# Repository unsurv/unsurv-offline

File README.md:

# unsurv-offline

Currently available on [crowdsupply](https://www.crowdsupply.com/unsurv-technologies/unsurv-offline)

This project is part of the unsurv framework to fight privacy invasive technologies in the offline world. unsurv-offline logs your encounters with surveillance cameras and creates a daily report for you via NFC to review in the unsurv-companion Android app.

Demo: https://vimeo.com/497241039

This device can easily be adapted to different use cases via the Arduino IDE. Arduino library + board integration are planned.

List of features

- ESP32 D4
- ublox M8C GNSS receiver
- RF430CL330H NFC 
- BMA400 accelerometer
- SD card reader
- MCP73831 single cell LiPo charging
- CH340 USB to Serial

Software:
- [unsurv-offline](https://github.com/unsurv/unsurv-offline/tree/master/software/unsurv-offline)
- [other examples](https://github.com/unsurv/unsurv-offline/tree/master/software/examples) (tap to log location, location logging + step counting)

Hardware:
- [PCB design](https://github.com/unsurv/unsurv-offline/tree/master/unsurv_offline_pcb/main) (KiCad files)
- [case design](https://github.com/unsurv/unsurv-offline/tree/master/case) (FreeCAD + STL files)

Special thanks to:

- SparkFun for maintaining the [ublox library](https://github.com/sparkfun/SparkFun_Ublox_Arduino_Library)
- [awong1900](https://github.com/awong1900/RF430CL330H_Shield) for his work on the RF430
- [kriswiner](https://github.com/kriswiner/BMA400) for his BMA400 library

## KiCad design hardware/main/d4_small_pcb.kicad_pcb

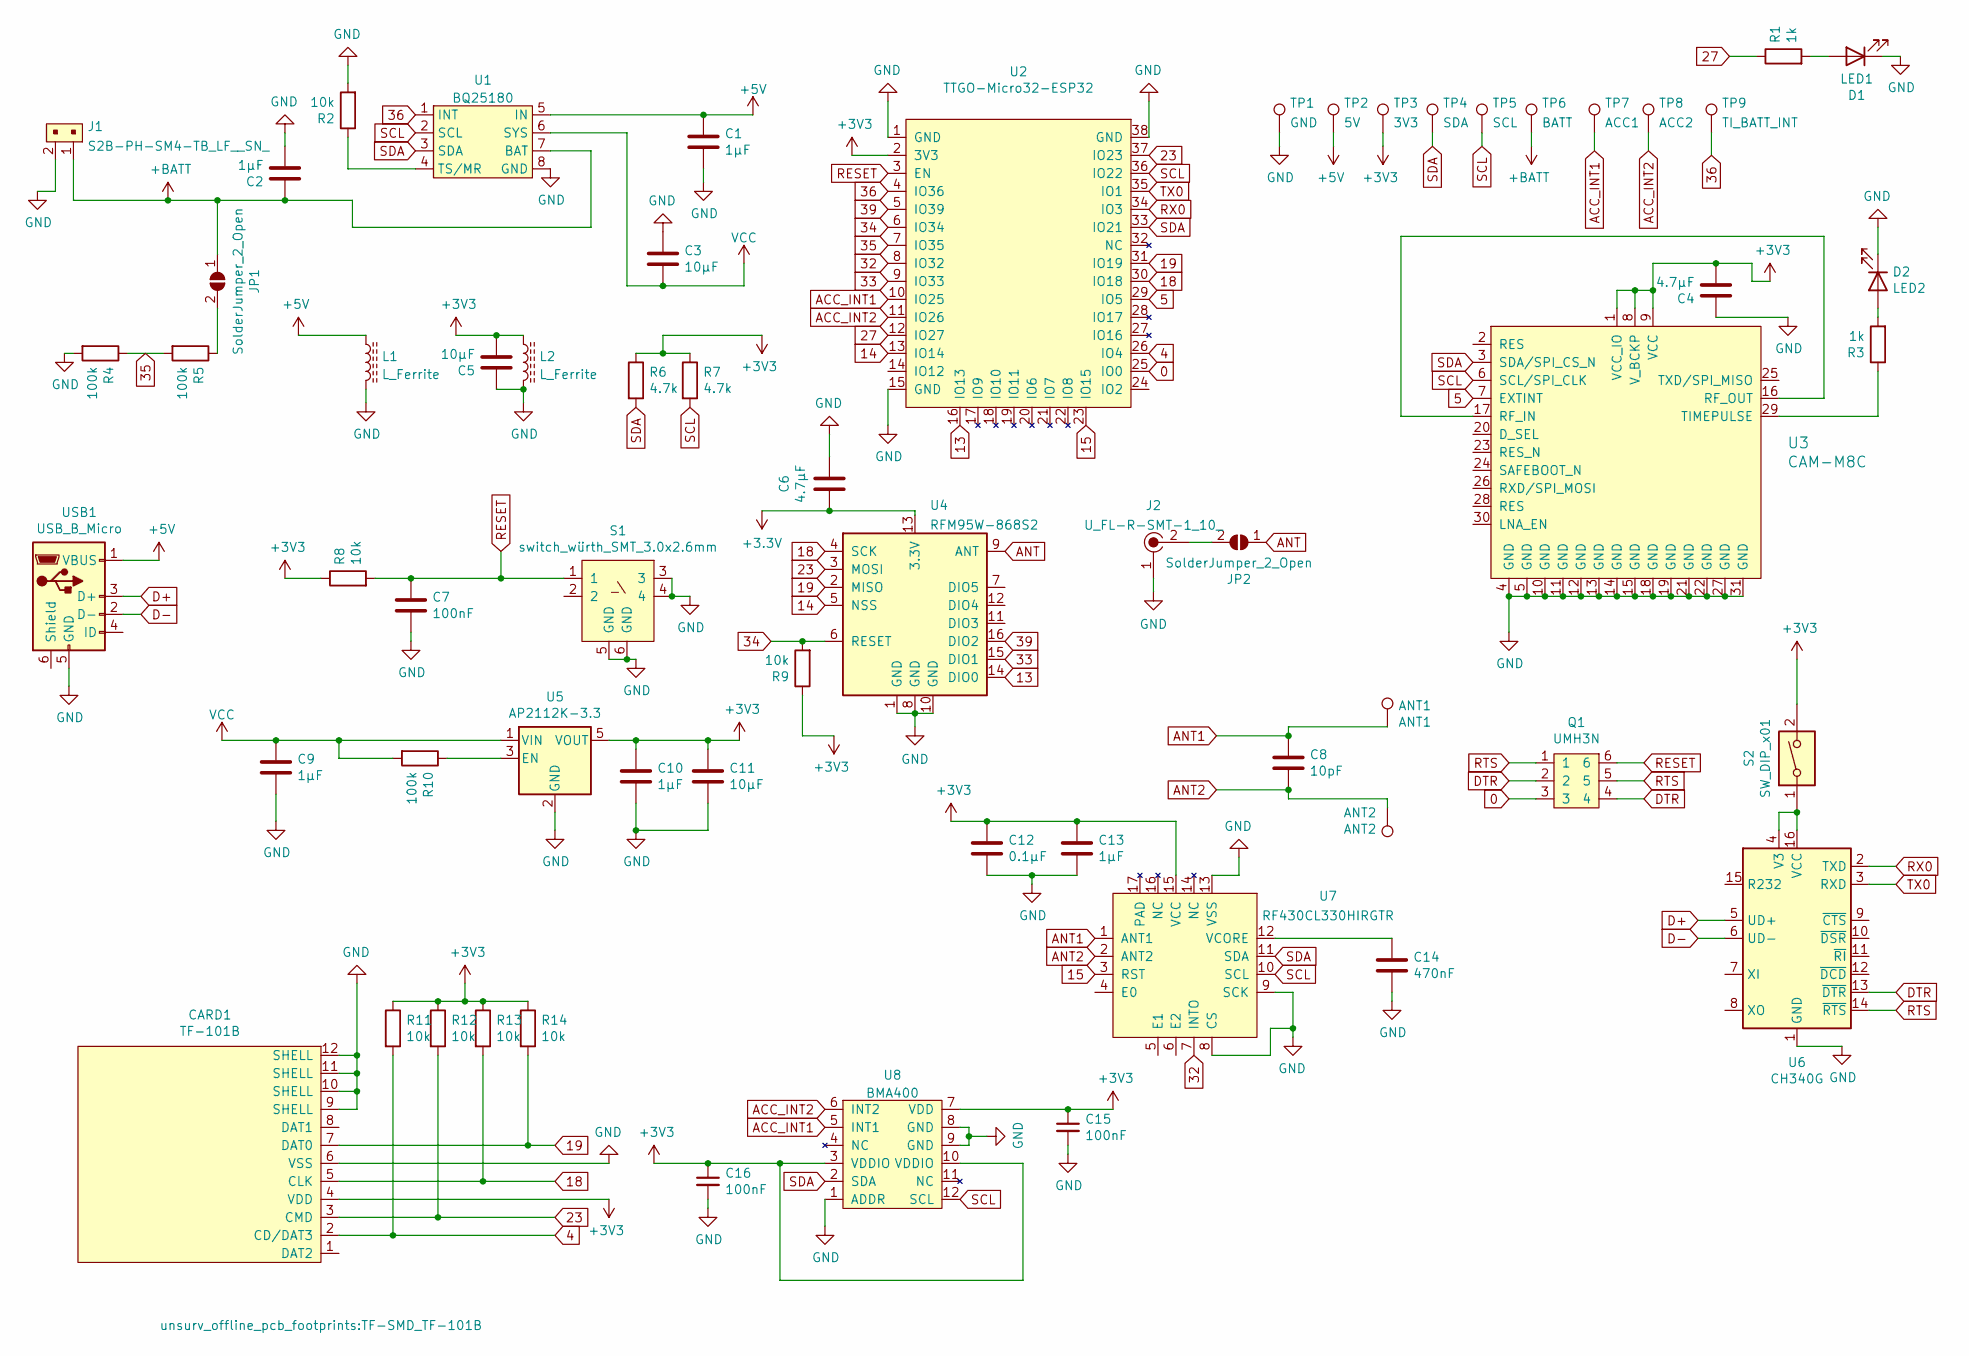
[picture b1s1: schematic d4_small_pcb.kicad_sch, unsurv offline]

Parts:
ANT1: ANT1; PogoPin_2_2mm_circular; MPN P70-1010045R
ANT2: ANT2; PogoPin_2_2mm_circular; MPN P70-1010045R
C1, C2, C9, C10, C13: 1µF; C_0603_1608Metric
C3, C5, C11: 10µF; C_0603_1608Metric
C4, C6: 4.7µF; C_0603_1608Metric
C7, C15, C16: 100nF; C_0603_1608Metric
C8: 10pF; C_0603_1608Metric
C12: 0.1µF; C_0603_1608Metric
C14: 470nF; C_0603_1608Metric
CARD1: TF-101B; TF-SMD_TF-101B; MPN TF-101B
D1: LED1; LED_0603
D2: LED2; LED_0603
J1: S2B-PH-SM4-TB_LF__SN_; PinHeader_2x1mm_P2mm_SMD_RA; MPN S2B-PH-SM4-TB(LF)(SN); Digi-Key_PN 455-1749-1-ND
J2: U_FL-R-SMT-1_10_; Coax_Conn_U.FL; MPN U.FL-R-SMT-1(10); Digi-Key_PN H11891CT-ND
JP1, JP2: SolderJumper_2_Open; SolderJumper-2_P1.3mm_Open_RoundedPad1.0x1.5mm
L1, L2: L_Ferrite; L_0603_1608Metric
Q1: UMH3N
R1, R3: 1k; R_0603_1608Metric
R2, R8, R9, R11, R12, R13, R14: 10k; R_0603_1608Metric
R4, R5, R10: 100k; R_0603_1608Metric
R6, R7: 4.7k; R_0603_1608Metric
S1: switch_würth_SMT_3.0x2.6mm; würth_SMT_3.0x2.6mm; MPN 435171014816
S2: SW_DIP_x01; CHS-01TA; MPN CHS-01TA
TP1: GND; TestPoint_Pad_D1.0mm
TP2: 5V; TestPoint_Pad_D1.0mm
TP3: 3V3; TestPoint_Pad_D1.0mm
TP4: SDA; TestPoint_Pad_D1.0mm
TP5: SCL; TestPoint_Pad_D1.0mm
TP6: BATT; TestPoint_Pad_D1.0mm
TP7: ACC1; TestPoint_Pad_D1.0mm
TP8: ACC2; TestPoint_Pad_D1.0mm
TP9: TI_BATT_INT; TestPoint_Pad_D1.0mm
U1: BQ25180; MPN BQ25180YBGR
U2: TTGO-Micro32-ESP32
U3: CAM-M8C; GPS_Module_CAM-M8C-0; MPN CAM-M8C-0-10; Digi-Key_PN 672-CAM-M8C-0-10CT-ND
U4: RFM95W-868S2; HOPERF_RFM9XW_SMD
U5: AP2112K-3.3; SOT-23-5
U6: CH340G; SOIC-16_3.9x9.9mm_P1.27mm
U7: RF430CL330HIRGTR‎; RF430_3x3mm_regular; MPN RF430CL330HIRGTR
U8: BMA400; BMA400_regular
USB1: USB_B_Micro; USB_Micro-B_Amphenol_10103594-0001LF_Horizontal; MPN 10103594-0001LF

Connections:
0: Q1.3, U2.25 (IO0)
4: CARD1.2 (CD/DAT3), R11.2, U2.26 (IO4)
5: U2.29 (IO5), U3.7 (EXTINT)
13: U2.16 (IO13), U4.14 (DIO0)
14: U2.13 (IO14), U4.5 (NSS)
15: U2.23 (IO15), U7.3 (RST)
18: CARD1.5 (CLK), R13.2, U2.30 (IO18), U4.4 (SCK)
19: CARD1.7 (DAT0), R14.2, U2.31 (IO19), U4.2 (MISO)
23: CARD1.3 (CMD), R12.2, U2.37 (IO23), U4.3 (MOSI)
27: R1.1, U2.12 (IO27)
32: U2.8 (IO32), U7.7 (INTO)
33: U2.9 (IO33), U4.15 (DIO1)
34: R9.2, U2.6 (IO34), U4.6 (RESET)
35: R4.1, R5.2, U2.7 (IO35)
36: TP9.1, U1.1 (INT), U2.4 (IO36)
39: U2.5 (IO39), U4.16 (DIO2)
+3.3V: C6.2, U4.13 (3.3V)
+3V3: C4.2, C5.1, C10.2, C11.2, C12.1, C13.1, C15.1, C16.1, CARD1.4 (VDD), L2.1, R6.1, R7.1, R8.1, R9.1, R11.1, R12.1, R13.1, R14.1, S2.2, TP3.1, U2.2 (3V3), U3.1 (VCC_IO), U3.8 (V_BCKP), U3.9 (VCC), U5.5 (VOUT), U7.15 (VCC), U8.3 (VDDIO), U8.7 (VDD), U8.10 (VDDIO)
+5V: C1.2, L1.1, TP2.1, U1.5 (IN), USB1.1 (VBUS)
+BATT: C2.2, J1.1, JP1.1 (A), TP6.1, U1.7 (BAT)
ACC_INT1: TP7.1, U2.10 (IO25), U8.5 (INT1)
ACC_INT2: TP8.1, U2.11 (IO26), U8.6 (INT2)
ANT: JP2.1 (A), U4.9 (ANT)
ANT1: ANT1.1, C8.1, U7.1 (ANT1)
ANT2: ANT2.1, C8.2, U7.2 (ANT2)
D+: U6.5 (UD+), USB1.3 (D+)
D-: U6.6 (UD-), USB1.2 (D-)
DTR: Q1.2, Q1.4, U6.13 (~DTR)
GND: C1.1, C2.1, C3.2, C4.1, C5.2, C6.1, C7.2, C9.1, C10.1, C11.1, C12.2, C13.2, C14.2, C15.2, C16.2, CARD1.6 (VSS), CARD1.9 (SHELL), CARD1.10 (SHELL), CARD1.11 (SHELL), CARD1.12 (SHELL), D1.1 (K), D2.1 (K), J1.2, J2.1, L1.2, L2.2, R2.2, R4.2, S1.3, S1.4, S1.5 (GND), S1.6 (GND), TP1.1, U1.8 (GND), U2.1 (GND), U2.15 (GND), U2.38 (GND), U3.4 (GND), U3.5 (GND), U3.10 (GND), U3.11 (GND), U3.12 (GND), U3.13 (GND), U3.14 (GND), U3.15 (GND), U3.18 (GND), U3.19 (GND), U3.21 (GND), U3.22 (GND), U3.27 (GND), U3.31 (GND), U4.1 (GND), U4.8 (GND), U4.10 (GND), U5.2 (GND), U6.1 (GND), U7.8 (CS), U7.9 (SCK), U7.13 (VSS), U8.1 (ADDR), U8.8 (GND), U8.9 (GND), USB1.5 (GND)
unnamed: D1.2 (A), R1.2
unnamed: D2.2 (A), R3.2
unnamed: JP1.2 (B), R5.1
unnamed: J2.2, JP2.2 (B)
unnamed: R2.1, U1.4 (TS/MR)
unnamed: U3.16 (RF_OUT), U3.17 (RF_IN)
unnamed: R3.1, U3.29 (TIMEPULSE)
unnamed: R10.1, U5.3 (EN)
unnamed: S2.1, U6.4 (V3), U6.16 (VCC)
unnamed: C14.1, U7.12 (VCORE)
RESET: C7.1, Q1.6, R8.2, S1.1, U2.3 (EN)
RTS: Q1.1, Q1.5, U6.14 (~RTS)
RX0: U2.34 (IO3), U6.2 (TXD)
SCL: R7.2, TP5.1, U1.2 (SCL), U2.36 (IO22), U3.6 (SCL/SPI_CLK), U7.10 (SCL), U8.12 (SCL)
SDA: R6.2, TP4.1, U1.3 (SDA), U2.33 (IO21), U3.3 (SDA/SPI_CS_N), U7.11 (SDA), U8.2 (SDA)
TX0: U2.35 (IO1), U6.3 (RXD)
VCC: C3.1, C9.2, R10.2, U1.6 (SYS), U5.1 (VIN)

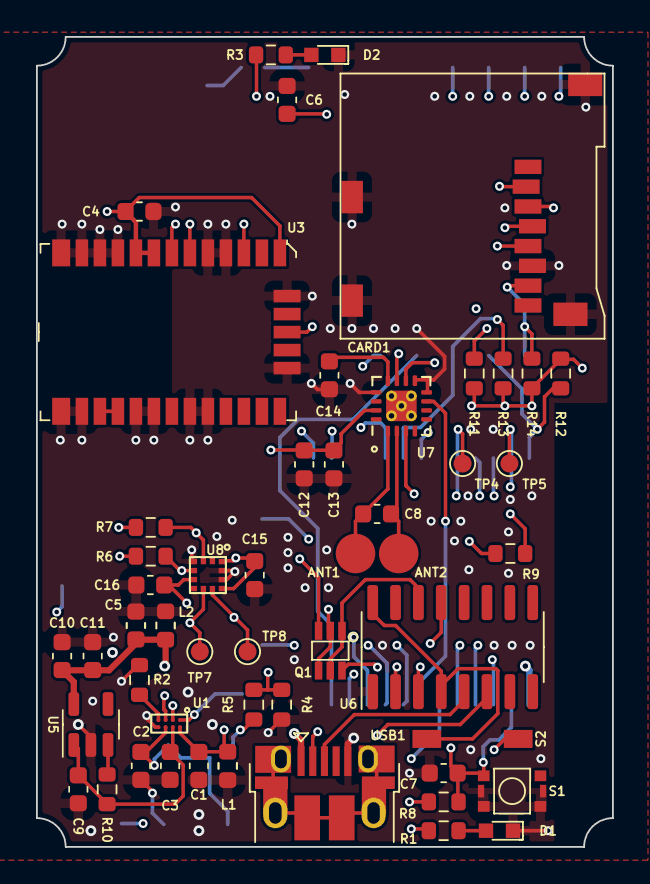
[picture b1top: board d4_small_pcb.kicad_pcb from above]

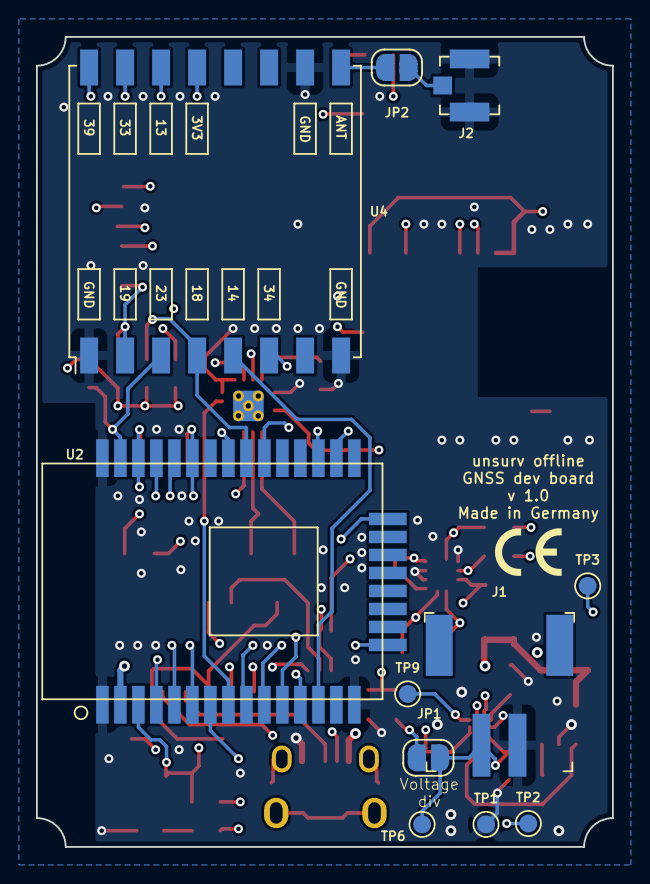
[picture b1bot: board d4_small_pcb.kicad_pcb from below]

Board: 4 copper layers, 32.0 x 45.0 mm, 62 parts (11 on the bottom side), 46 nets.

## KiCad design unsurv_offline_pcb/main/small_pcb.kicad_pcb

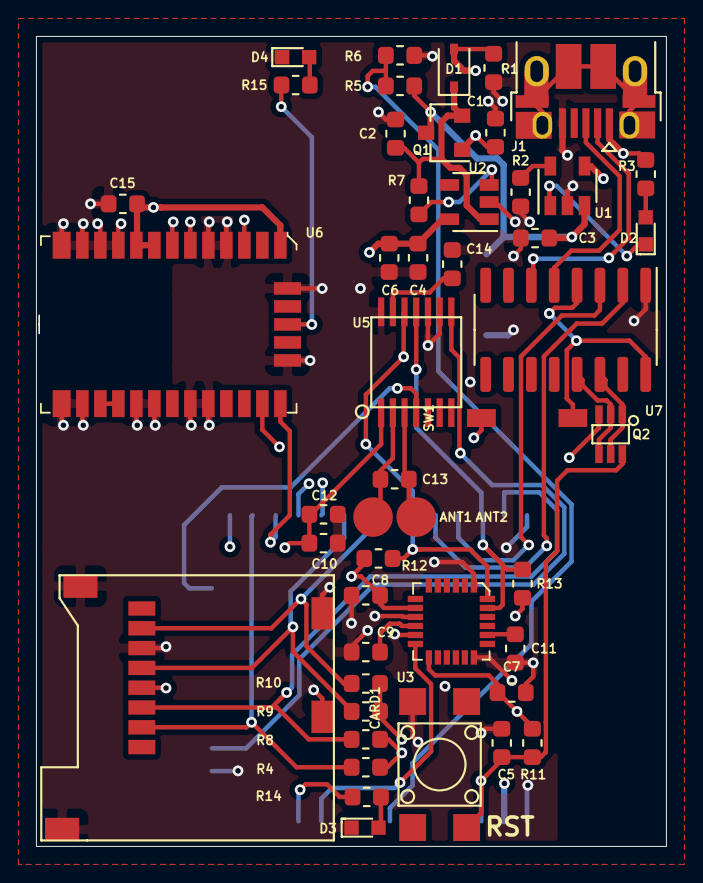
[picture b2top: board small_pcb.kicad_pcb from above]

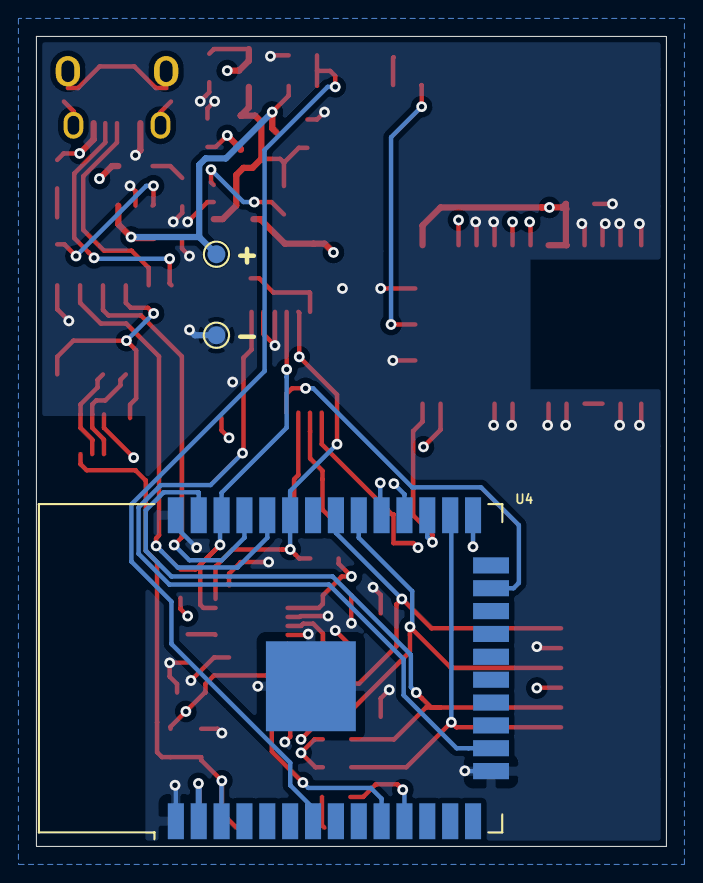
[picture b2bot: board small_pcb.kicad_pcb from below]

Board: 4 copper layers, 35.0 x 45.0 mm, 51 parts (3 on the bottom side), 41 nets.

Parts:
+: +; TestPoint_Pad_D1.0mm
-: -; TestPoint_Pad_D1.0mm
ANT1, ANT2: TestPoint; PogoPin_2_2mm_circular
C1, C3: 4.7yF; C_0603_1608Metric
C2, C4, C12: 1yF; C_0603_1608Metric
C5: 100nF; C_0603_1608Metric
C6: 10yF; C_0603_1608Metric
C7, C9, C10: 0.1yF; C_0603_1608Metric
C8: 10nF; C_0603_1608Metric
C11: 2.2nF; C_0603_1608Metric
C13: 10pF; C_0603_1608Metric
C14: 470nF; C_0603_1608Metric
C15: 2.2yF; C_0603_1608Metric
CARD1: TF-101B; TF-SMD_TF-101B
D1: D_Schottky; D_SOD-323
D2, D3, D4: LED; LED_0603
J1: USB_B_Micro; USB_Micro-B_Amphenol_10103594-0001LF_Horizontal
Q1: Q_PMOS_GSD; SOT-23
Q2: UMH3N
R1, R2, R4, R8, R9, R10, R11: 10k; R_0603_1608Metric
R3, R14, R15: 1k; R_0603_1608Metric
R5, R6, R7: 100k; R_0603_1608Metric
R12, R13: 4.7k; R_0603_1608Metric
RST: 2x2_switch; 2x2 Switch
SW1: SW_DIP_x01; CHS-01TA
U1: MCP73831-2-OT; SOT-23-5
U2: AP2112K-3.3; SOT-23-5
U3: MPU-6050_NRND; QFN-24-1EP_4x4mm
U4: ESP32-WROOM-32
U5: RF430CL330H
U6: CAM-M8C-0-10; GPS_Module_CAM-M8C-0
U7: CH340G; SOIC-16_3.9x9.9mm_P1.27mm

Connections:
0: Q2.3, U4.25
4: CARD1.2, R4.2, U4.26
5: U4.29, U6.7
13: U4.16, U5.8
15: U4.23, U5.4
18: CARD1.5, R9.2, U4.30
19: CARD1.7, R10.2, U4.31
23: CARD1.3, R8.2, U4.37
26: R14.1, U4.11
35: R5.2, R6.1, U4.7
+3V3: C4.2, C6.2, C7.1, C8.2, C10.1, C12.1, C15.2, CARD1.4, R4.1, R8.1, R9.1, R10.1, R11.1, R12.1, R13.1, SW1.2, U2.5, U3.8, U3.13, U4.2, U5.1, U6.1, U6.8, U6.9
+5V: C1.2, D1.2, J1.1, Q1.1, R1.2, R3.2, U1.4
+BATT: +.1, C3.2, Q1.3, R5.1, U1.3
ACC_INT: U3.12, U4.10
ANT1: ANT1.1, C13.1, U5.2
ANT2: ANT2.1, C13.2, U5.3
D+: J1.3, U7.5
D-: J1.2, U7.6
DTR: Q2.2, Q2.4, U7.13
GND: -.1, C1.1, C2.1, C3.1, C4.1, C5.2, C6.1, C7.2, C8.1, C9.2, C10.2, C11.2, C12.2, C14.2, C15.1, CARD1.6, CARD1.9, CARD1.10, CARD1.11, CARD1.12, D3.1, D4.1, J1.5, R1.1, R2.2, R6.2, RST.4, U1.2, U2.2, U3.1, U3.9, U3.11, U3.18, U4.1, U4.15, U4.38, U4.39, U5.9, U5.10, U5.14, U6.4, U6.5, U6.10, U6.11, U6.12, U6.13, U6.14, U6.15, U6.18, U6.19, U6.21, U6.22, U6.27, U6.31, U7.1
unnamed: C2.2, D1.1, Q1.2, R7.2, U2.1
unnamed: C9.1, U3.10
unnamed: C11.1, U3.20
unnamed: C14.1, U5.13
unnamed: D2.1, U1.1
unnamed: D2.2, R3.1
unnamed: D3.2, R14.2
unnamed: D4.2, R15.2
unnamed: R2.1, U1.5
unnamed: R7.1, U2.3
unnamed: R15.1, U6.29
unnamed: SW1.1, U7.4, U7.16
unnamed: U6.16, U6.17
RESET: C5.1, Q2.6, R11.2, RST.1, U4.3
RTS: Q2.1, Q2.5, U7.14
RX0: U4.34, U7.2
RX2: U4.27, U6.26
SCL: R13.2, U3.23, U4.36, U5.11, U6.6
SDA: R12.2, U3.24, U4.33, U5.12, U6.3
TX0: U4.35, U7.3
TX2: U4.28, U6.25

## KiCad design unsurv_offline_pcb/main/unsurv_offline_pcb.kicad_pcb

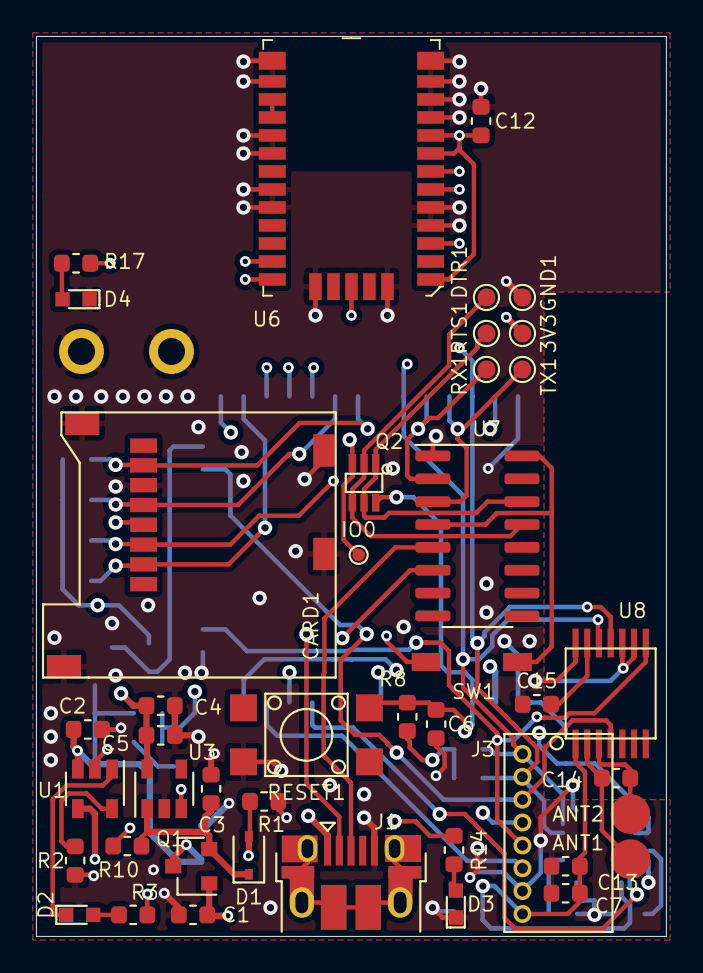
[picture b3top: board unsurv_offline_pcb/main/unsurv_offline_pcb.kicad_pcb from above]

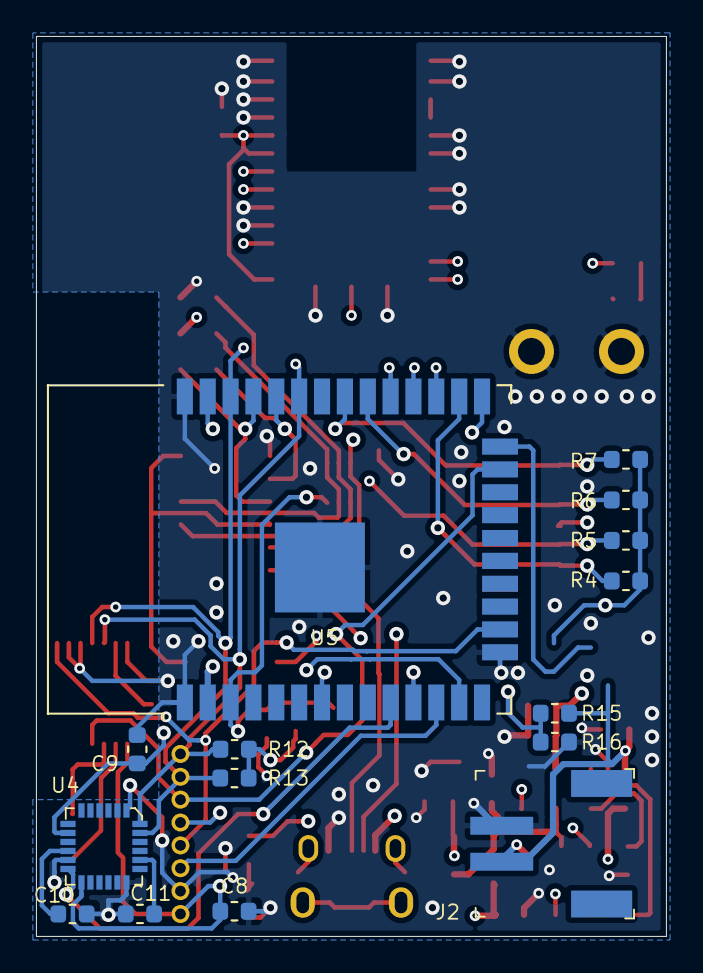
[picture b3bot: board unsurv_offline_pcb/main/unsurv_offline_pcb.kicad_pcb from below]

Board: 4 copper layers, 35.0 x 50.0 mm, 60 parts (15 on the bottom side), 43 nets.

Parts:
3V3: TestPoint; TestPoint_Pad_D1.0mm
ANT1, ANT2: TestPoint; PogoPin_2_2mm_circular
C1, C2: 4.7yF; C_0603_1608Metric
C3, C4, C13: 1yF; C_0603_1608Metric
C5: 10yF; C_0603_1608Metric
C6: 100nF; C_0603_1608Metric
C7, C8, C10: 0.1yF; C_0603_1608Metric
C9: 10nF; C_0603_1608Metric
C11: 2.2nF; C_0603_1608Metric
C12: 2.2yF; C_0603_1608Metric
C14: 10pF; C_0603_1608Metric
C15: 470nF; C_0603_1608Metric
CARD1: TF-101B; TF-SMD_TF-101B
D1: D_Schottky; D_SOD-323
D2, D3, D4: LED; LED_0603
DTR1: TestPoint; TestPoint_Pad_D1.0mm
GND1: TestPoint; TestPoint_Pad_D1.0mm
H1, H2: MountingHole_Pad; MountingHole_1.5mm_hole_in_FPaste
IO0: TestPoint; TestPoint_Pad_D0.7mm
J1: USB_B_Micro; USB_Micro-B_Amphenol_10103594-0001LF_Horizontal
J2: S2B-PH-SM4-TB_LF__SN_; PinHeader_2x1mm_P2mm_SMD_RA
J3: 1.27mm_female_connector; LPPB081NGCN-RC
Q1: Q_PMOS_GSD; SOT-23
Q2: UMH3N
R1, R4, R5, R6, R7, R8: 10k; R_0603_1608Metric
R2: 2k; R_0603_1608Metric
R3, R14, R17: 1k; R_0603_1608Metric
R10, R15, R16: 100k; R_0603_1608Metric
R12, R13: 4.7k; R_0603_1608Metric
RESET1: 2x2_switch; 2x2 Switch
RTS1: TestPoint; TestPoint_Pad_D1.0mm
RX1: TestPoint; TestPoint_Pad_D1.0mm
SW1: SW_DIP_x01; CHS-01TA
TX1: TestPoint; TestPoint_Pad_D1.0mm
U1: MCP73831-2-OT; SOT-23-5
U3: AP2112K-3.3; SOT-23-5
U4: MPU-6050_NRND; QFN-24-1EP_4x4mm
U5: ESP32-WROOM-32
U6: CAM-M8C-0-10; GPS_Module_CAM-M8C-0
U7: CH340G; SOIC-16_3.9x9.9mm_P1.27mm
U8: RF430CL330H

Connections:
0: IO0.1, Q2.3, U5.25
4: CARD1.2, R4.2, U5.26
5: U5.29, U6.7
13: J3.4, U5.16, U8.8
14: J3.5, U5.13
15: J3.6, U5.23, U8.4
18: CARD1.5, R6.2, U5.30
19: CARD1.7, R7.2, U5.31
23: CARD1.3, R5.2, U5.37
26: R14.1, U5.11
27: J3.3, U5.12
35: R15.2, R16.1, U5.7
+3V3: 3V3.1, C4.2, C5.2, C7.1, C8.1, C9.2, C12.2, C13.1, CARD1.4, J3.1, R4.1, R5.1, R6.1, R7.1, R8.1, R12.1, R13.1, SW1.2, U3.5, U4.8, U4.13, U5.2, U6.1, U6.8, U6.9, U8.1
+5V: C1.2, D1.2, J1.1, Q1.1, R1.2, R3.2, U1.4
+BATT: C2.2, J2.2, Q1.3, R15.1, U1.3
ACC_INT: U4.12, U5.10
ANT1: ANT1.1, C14.1, U8.2
ANT2: ANT2.1, C14.2, U8.3
D+: J1.3, U7.5
D-: J1.2, U7.6
DTR: DTR1.1, Q2.2, Q2.4, U7.13
GND: C1.1, C2.1, C3.1, C4.1, C5.1, C6.2, C7.2, C8.2, C9.1, C10.2, C11.2, C12.1, C13.2, C15.2, CARD1.6, CARD1.9, CARD1.10, CARD1.11, CARD1.12, D3.1, D4.1, GND1.1, H1.1, H2.1, J1.5, J2.1, J3.2, R1.1, R2.2, R16.2, RESET1.4, U1.2, U3.2, U4.1, U4.11, U4.18, U5.1, U5.15, U5.38, U5.39, U6.4, U6.5, U6.10, U6.11, U6.12, U6.13, U6.14, U6.15, U6.18, U6.19, U6.21, U6.22, U6.27, U6.31, U7.1, U8.9, U8.10, U8.14
unnamed: C3.2, D1.1, Q1.2, R10.2, U3.1
unnamed: C10.1, U4.10
unnamed: C11.1, U4.20
unnamed: C15.1, U8.13
unnamed: D2.1, U1.1
unnamed: D2.2, R3.1
unnamed: D3.2, R14.2
unnamed: D4.2, R17.2
unnamed: R2.1, U1.5
unnamed: R10.1, U3.3
unnamed: R17.1, U6.29
unnamed: SW1.1, U7.4, U7.16
unnamed: U6.16, U6.17
RESET: C6.1, Q2.6, R8.2, RESET1.1, U5.3
RTS: Q2.1, Q2.5, RTS1.1, U7.14
RX0: RX1.1, U5.34, U7.2
RX2: U5.27, U6.26
SCL: J3.7, R13.2, U4.23, U5.36, U6.6, U8.11
SDA: J3.8, R12.2, U4.24, U5.33, U6.3, U8.12
TX0: TX1.1, U5.35, U7.3
TX2: U5.28, U6.25

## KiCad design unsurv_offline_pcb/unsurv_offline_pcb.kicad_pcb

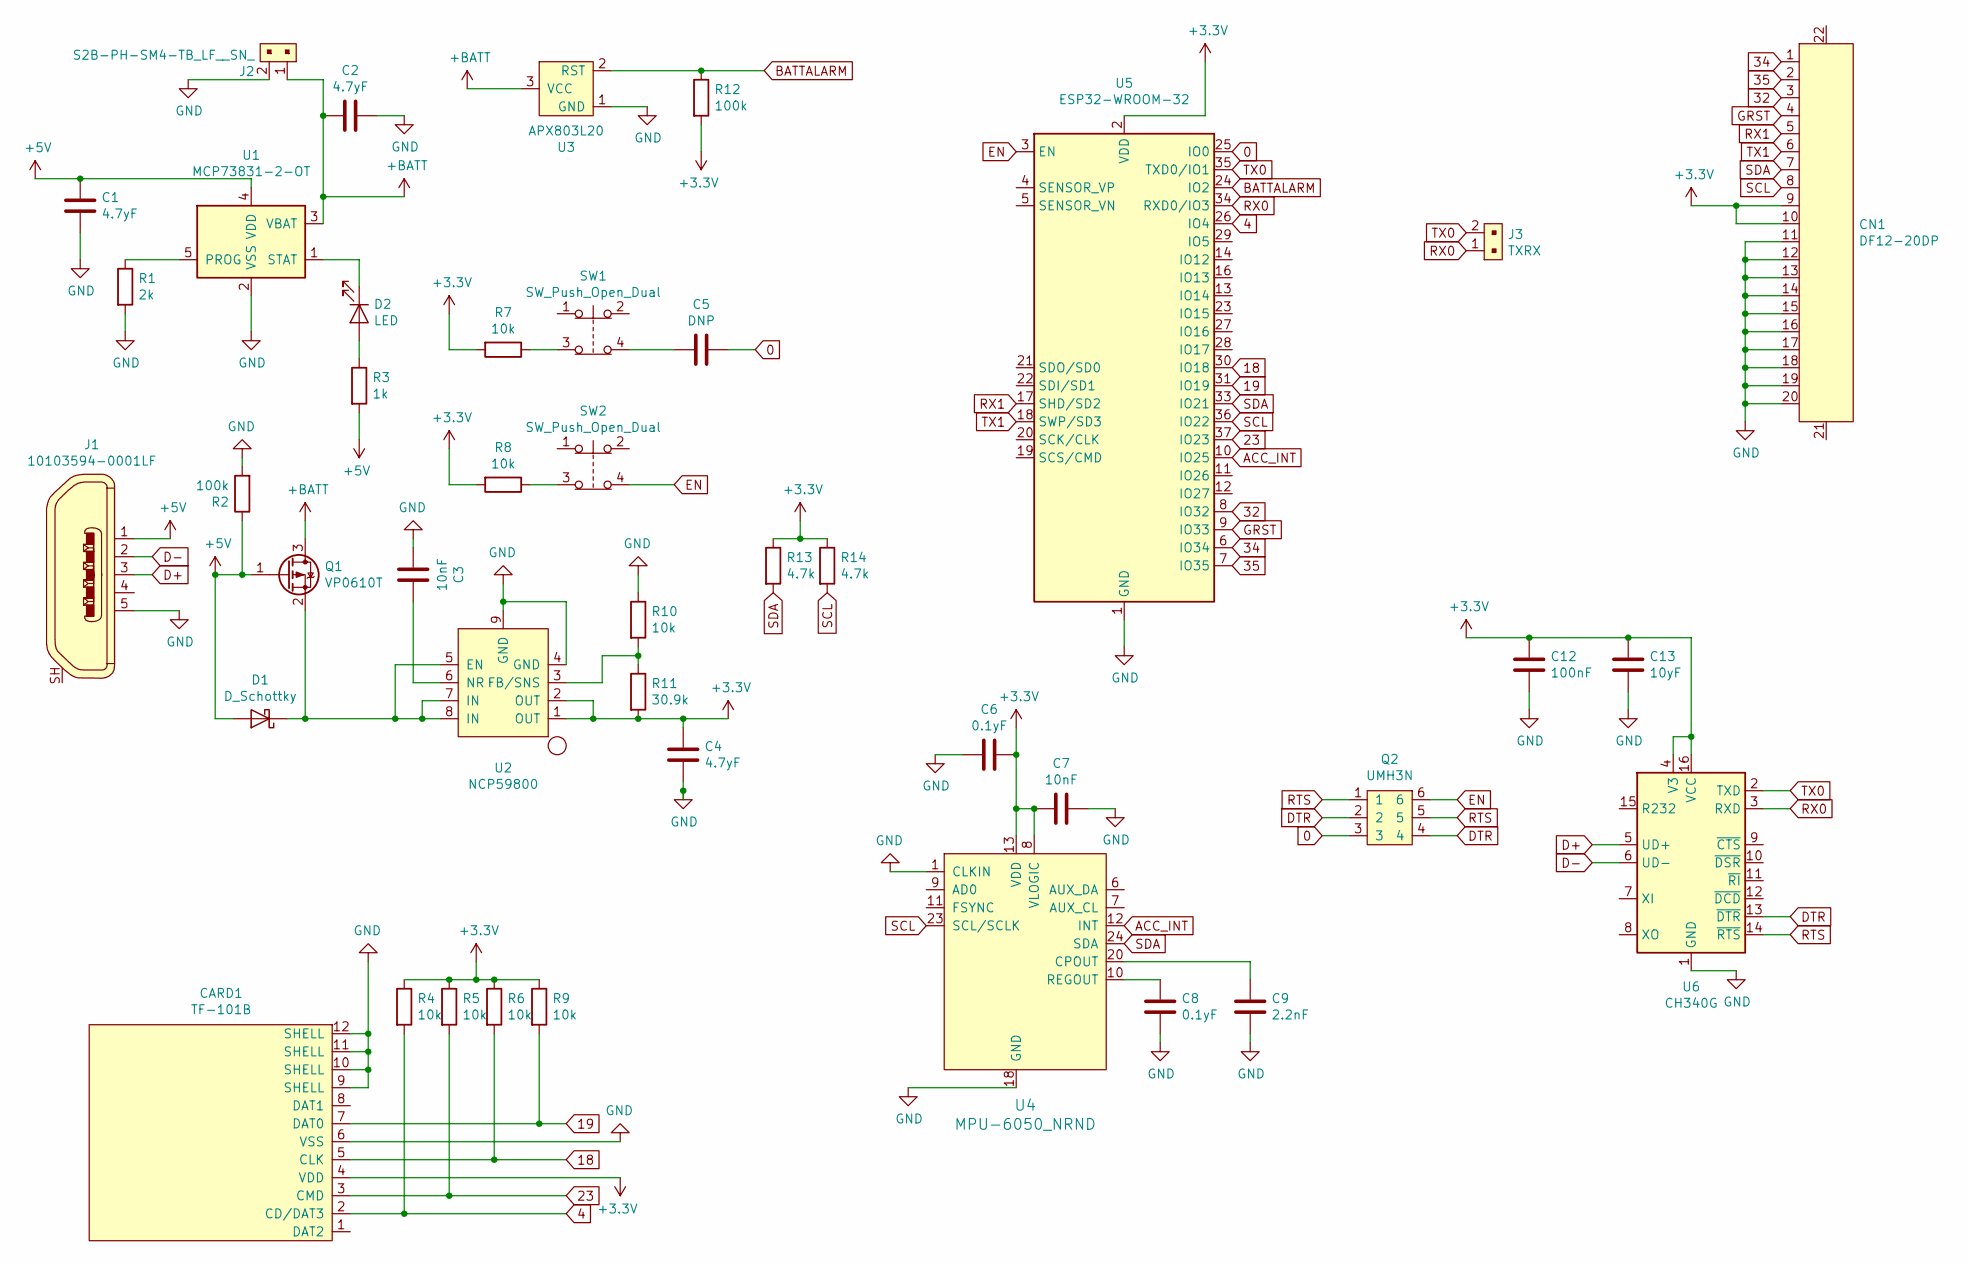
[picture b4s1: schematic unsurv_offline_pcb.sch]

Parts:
C1, C2, C4: 4.7yF; C_0603_1608Metric
C3, C7: 10nF; C_0603_1608Metric
C5: DNP; C_0603_1608Metric
C6, C8: 0.1yF; C_0603_1608Metric
C9: 2.2nF; C_0603_1608Metric
C12: 100nF; C_0603_1608Metric
C13: 10yF; C_0603_1608Metric
CARD1: TF-101B; TF-SMD_TF-101B
CN1: DF12-20DP; DF-12-20DP
D1: D_Schottky; D_SOD-323
D2: LED; LED_0603
J1: 10103594-0001LF; USB_Micro_B_Female_10103594-0001LF; MPN 10103594-0001LF; Digi-Key_PN 609-4050-1-ND
J2: S2B-PH-SM4-TB_LF__SN_; PinHeader_2x1mm_P2mm_SMD_RA; MPN S2B-PH-SM4-TB(LF)(SN); Digi-Key_PN 455-1749-1-ND
J3: TXRX; PinHeader_1x2_P2.54mm_Drill1.02mm; MPN 22-23-2021; Digi-Key_PN WM4200-ND
Q1: VP0610T; SOT-23
Q2: UMH3N
R1: 2k; R_0603_1608Metric
R2, R12: 100k; R_0603_1608Metric
R3: 1k; R_0603_1608Metric
R4, R5, R6, R7, R8, R9, R10: 10k; R_0603_1608Metric
R11: 30.9k; R_0603_1608Metric
R13, R14: 4.7k; R_0603_1608Metric
SW1, SW2: SW_Push_Open_Dual; 2x2 Switch
U1: MCP73831-2-OT; SOT-23-5
U2: NCP59800
U3: APX803L20; SOT-23-3
U4: MPU-6050_NRND; QFN-24-1EP_4x4mm; MPN MPU-6050; Digi-Key_PN 1428-1007-1-ND
U5: ESP32-WROOM-32
U6: CH340G; SOIC-16_3.9x9.9mm_P1.27mm

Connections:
0: C5.1, Q2.3, U5.25 (IO0)
4: CARD1.2 (CD/DAT3), R4.2, U5.26 (IO4)
18: CARD1.5 (CLK), R6.2, U5.30 (IO18)
19: CARD1.7 (DAT0), R9.2, U5.31 (IO19)
23: CARD1.3 (CMD), R5.2, U5.37 (IO23)
32: CN1.3, U5.8 (IO32)
34: CN1.1, U5.6 (IO34)
35: CN1.2, U5.7 (IO35)
+3V3: C4.1, C6.1, C7.2, C12.1, C13.1, CARD1.4 (VDD), CN1.9, CN1.10, R4.1, R5.1, R6.1, R7.2, R8.2, R9.1, R11.2, R12.2, R13.1, R14.1, U2.1 (OUT), U2.2 (OUT), U4.8 (VLOGIC), U4.13 (VDD), U5.2 (VDD), U6.4 (V3), U6.16 (VCC)
+5V: C1.2, D1.2 (A), J1.1, Q1.1 (G), R2.1, R3.2, U1.4 (VDD)
+BATT: C2.2, J2.1, Q1.3 (D), U1.3 (VBAT), U3.3 (VCC)
ACC_INT: U4.12 (INT), U5.10 (IO25)
BATTALARM: R12.1, U3.2 (RST), U5.24 (IO2)
D+: J1.3, U6.5 (UD+)
D-: J1.2, U6.6 (UD-)
DTR: Q2.2, Q2.4, U6.13 (~DTR)
EN: Q2.6, SW2.4, U5.3 (EN)
GND: C1.1, C2.1, C3.2, C4.2, C6.2, C7.1, C8.2, C9.2, C12.2, C13.2, CARD1.6 (VSS), CARD1.9 (SHELL), CARD1.10 (SHELL), CARD1.11 (SHELL), CARD1.12 (SHELL), CN1.11, CN1.12, CN1.13, CN1.14, CN1.15, CN1.16, CN1.17, CN1.18, CN1.19, CN1.20, J1.5, J2.2, R1.2, R2.2, R10.1, U1.2 (VSS), U2.4 (GND), U2.9 (GND), U3.1 (GND), U4.1 (CLKIN), U4.18 (GND), U5.1 (GND), U5.15 (GND), U5.38 (GND), U5.39 (GND), U6.1 (GND)
GRST: CN1.4, U5.9 (IO33)
unnamed: C3.1, U2.6 (NR)
unnamed: C5.2, SW1.4
unnamed: C8.1, U4.10 (REGOUT)
unnamed: C9.1, U4.20 (CPOUT)
unnamed: D1.1 (K), Q1.2 (S), U2.5 (EN), U2.7 (IN), U2.8 (IN)
unnamed: D2.1 (K), U1.1 (STAT)
unnamed: D2.2 (A), R3.1
unnamed: R1.1, U1.5 (PROG)
unnamed: R7.1, SW1.3
unnamed: R8.1, SW2.3
unnamed: R10.2, R11.1, U2.3 (FB/SNS)
RTS: Q2.1, Q2.5, U6.14 (~RTS)
RX0: J3.1, U5.34 (RXD0/IO3), U6.3 (RXD)
RX1: CN1.5, U5.17 (SHD/SD2)
SCL: CN1.8, R14.2, U4.23 (SCL/SCLK), U5.36 (IO22)
SDA: CN1.7, R13.2, U4.24 (SDA), U5.33 (IO21)
TX0: J3.2, U5.35 (TXD0/IO1), U6.2 (TXD)
TX1: CN1.6, U5.18 (SWP/SD3)

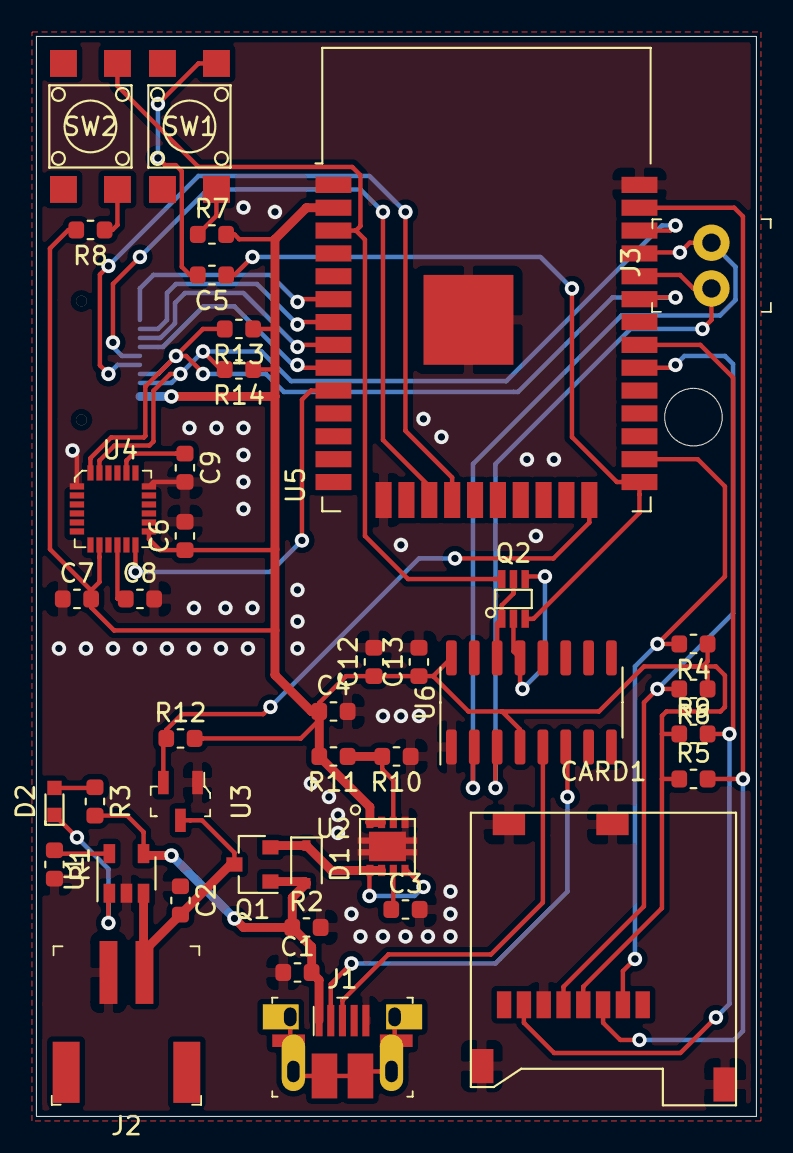
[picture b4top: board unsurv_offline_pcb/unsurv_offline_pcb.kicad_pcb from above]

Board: 2 copper layers, 40.0 x 60.0 mm, 42 parts (1 on the bottom side), 37 nets.

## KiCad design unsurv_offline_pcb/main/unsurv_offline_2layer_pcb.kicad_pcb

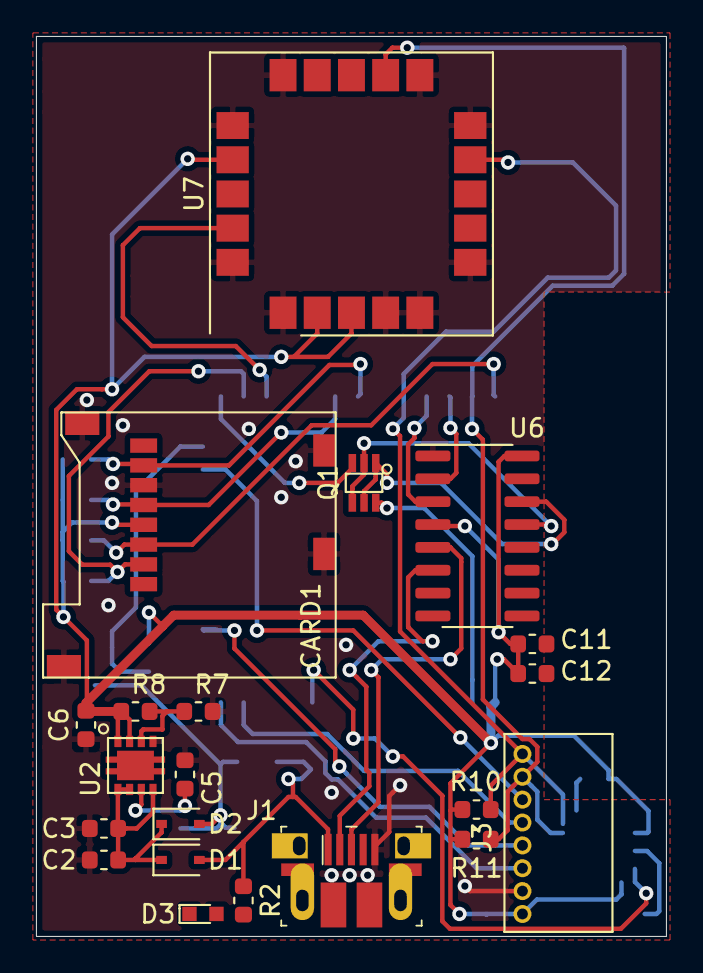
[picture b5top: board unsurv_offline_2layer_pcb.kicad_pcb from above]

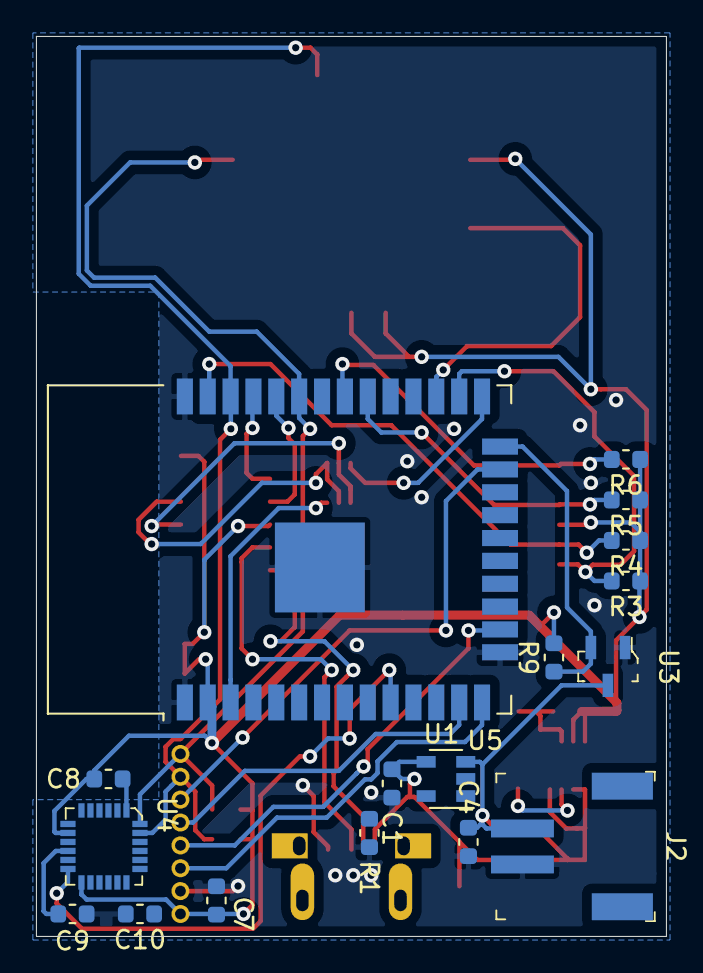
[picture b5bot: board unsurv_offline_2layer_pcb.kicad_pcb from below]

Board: 2 copper layers, 35.0 x 50.0 mm, 38 parts (17 on the bottom side), 33 nets.

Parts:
C1, C4, C6: 4.7yF; C_0603_1608Metric
C2, C11: 100nF; C_0603_1608Metric
C3: 1yF; C_0603_1608Metric
C5, C8: 10nF; C_0603_1608Metric
C7, C9: 0.1yF; C_0603_1608Metric
C10: 2.2nF; C_0603_1608Metric
C12: 10yF; C_0603_1608Metric
CARD1: TF-101B; TF-SMD_TF-101B
D1, D2: D_Schottky; D_SOD-323
D3: LED; LED_0603
J1: 10103594-0001LF; USB_Micro_B_Female_10103594-0001LF
J2: S2B-PH-SM4-TB_LF__SN_; PinHeader_2x1mm_P2mm_SMD_RA
J3: 1.27mm_female_connector; LPPB081NGCN-RC
Q1: UMH3N
R1: 2k; R_0603_1608Metric
R2: 1k; R_0603_1608Metric
R3, R4, R5, R6, R7: 10k; R_0603_1608Metric
R8: 30.9k; R_0603_1608Metric
R9: 100k; R_0603_1608Metric
R10, R11: 4.7k; R_0603_1608Metric
U1: MCP73831-2-OT; SOT-23-5
U2: NCP59800
U3: APX803L20; SOT-23-3
U4: MPU-6050_NRND; QFN-24-1EP_4x4mm
U5: ESP32-WROOM-32
U6: CH340G; SOIC-16_3.9x9.9mm_P1.27mm
U7: ublox_SAM-M8Q

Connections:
0: Q1.3, U5.25
4: CARD1.2, R3.2, U5.26
12: J3.3, U5.14
13: J3.4, U5.16
14: J3.5, U5.13
15: J3.6, U5.23
16: U5.27, U7.19
18: CARD1.5, R5.2, U5.30
19: CARD1.7, R6.2, U5.31
23: CARD1.3, R4.2, U5.37
+3V3: C6.1, C7.1, C8.2, C11.1, C12.1, CARD1.4, J3.1, R3.1, R4.1, R5.1, R6.1, R8.2, R9.2, R10.1, R11.1, U2.1, U2.2, U4.8, U4.13, U5.2, U6.4, U6.16, U7.2, U7.3, U7.17
+5V: C1.2, D1.2, J1.1, R2.2, U1.4
+BATT: C4.2, D2.2, J2.1, U1.3, U3.3
ACC_INT: U4.12, U5.10
BATTALARM: R9.1, U3.2, U5.24
D+: J1.3, U6.5
D-: J1.2, U6.6
DTR: Q1.2, Q1.4, U6.13
EN: Q1.6, U5.3
GND: C1.1, C2.2, C3.2, C4.1, C5.2, C6.2, C7.2, C8.1, C9.2, C10.2, C11.2, C12.2, CARD1.6, CARD1.9, CARD1.10, CARD1.11, CARD1.12, J1.5, J2.2, J3.2, R1.2, R7.1, U1.2, U2.4, U2.9, U3.1, U4.1, U4.18, U5.1, U5.15, U5.38, U5.39, U6.1, U7.1, U7.4, U7.5, U7.6, U7.10, U7.11, U7.15, U7.16, U7.20
unnamed: C2.1, C3.1, D1.1, D2.1, U2.5, U2.7, U2.8
unnamed: C5.1, U2.6
unnamed: C9.1, U4.10
unnamed: C10.1, U4.20
unnamed: D3.1, U1.1
unnamed: D3.2, R2.1
unnamed: R1.1, U1.5
unnamed: R7.2, R8.1, U2.3
RTS: Q1.1, Q1.5, U6.14
RX0: U5.34, U6.3
SCL: J3.7, R11.2, U4.23, U5.36, U7.12
SDA: J3.8, R10.2, U4.24, U5.33, U7.9
TX0: U5.35, U6.2

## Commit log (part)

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2019-07-08 test commit
2019-07-08 test II
2019-07-08 added SSD1327 128x128 display support
2019-07-22 added basic wifi scanner
    will be used to detect wifi networks with multiple APs which allows tracking of devices
2019-07-22 capture BSSIDs on a per SSID basis
2019-08-13 sleep on no motion, wakeup on motion for esp32
2019-08-13 comments
2019-08-13 explanations of mpu-6050 modes
2019-08-18 reads csv data from SD card
    Loads data from a csv file on an SD card that is considered in proximity to the device location.
2019-08-23 combined interrupt wakeup and data from SD card
2019-10-06 WEMOS D32 PRO + rf430 NFC "Hello world!" payload
2019-10-06 changing NFC payload
2019-10-29 added variable nfc tag
2020-04-03 changed from EasyEDA to KiCad
2020-04-04 Revert "changed from EasyEDA to KiCad"
    This reverts commit 82435eca3ce34d20457a26c89086bcd967547cae.
2020-04-04 Revert "Create .gitignore"
    This reverts commit 543a354852bbf98c6e17fbb30cfcc28cf880b4b0.
2020-04-04 changed from EasyEDA to KiCad
    this time with less files
2020-04-04 organizing files
2020-04-04 added schematic for addon board
2020-04-05 added DF40C-20 footprints
2020-04-06 added NFC-GPS pcb
2020-04-08 added power switch for GPS
2020-05-14 changed GPS code to Sparkfun ublox codebase
2020-05-14 added BluetoothSerial for debugging
2020-05-14 added LocationUtils
2020-05-14 added distance measuring when GPS aquired
2020-05-20 started basic case
2020-06-12 simplified power input
2020-06-13 reworked data retrieval from SD
2020-06-14 added location dependent SD query to main
2020-06-14 updated BT_Serial
2020-06-15 added rf430cl330 support into the main routine
2020-06-27 reducing pcb size
2020-06-27 placing components on small pcb
2020-06-29 created small pcb with 4 layers
2020-07-04 added addressable LED
2020-07-10 pcb work
2020-07-12 added testpoints
2020-07-12 added battery monitoring circuit
2020-07-15 fixed microvias
2020-07-18 added pps LED + fixed F.Mask
2020-07-20 3.5 cm x 5 cm prototype
2020-07-21 no conn to pin 12, defines memory voltage at boot
2020-08-09 fixed NCP59800 footprint
2020-08-20 charging circuit cleanup + new GPS
2020-08-23 improved routing + less vias
2020-08-24 Update LICENSE
2020-08-30 USB power/ lipo charging part 27
2020-08-30 USB power/ lipo charging part 28
2020-09-01 added 3x2 pads for pogo pins
2020-09-21 added RF430CL330H to schematic
2020-09-22 added RF430CL330H to pcb
2020-09-23 bottom case
2020-09-23 top case
2020-09-25 power save test
2020-09-27 fixed microSD cutout
2020-09-27 top case 3D printing file
2020-09-28 started smaller pcb version
2020-10-02 reduced pcb size
2020-10-07 finalized smaller pcb
2020-10-11 added motion activation + code refactoring
2020-10-19 added small case
2020-10-20 added NFC communication
2020-10-21 fixed no motion sleep
2020-10-23 lowered power consumption in deep sleep
2020-10-24 added longer search time if no satellite in view
2020-10-31 updated sleeping method to save more power
2020-11-01 stopped freezing when no SD card present
2020-11-07 fixed power consumption while savePower is active
2020-11-11 added logging to SD + GPS powerSave
2020-11-19 better clips for case
2020-11-20 changed order of charge LED
2020-11-20 nfc in JSON format
2020-11-20 increased min satellites in view before logging
2020-11-20 changedcase edges
2020-11-21 tweaked nfc JSON format
2020-11-23 logging contacts to SD
2020-11-27 minized NFC data
2020-11-27 fixed JSON naming
2020-11-28 minimized NFC data pt II
2020-11-29 read last contacts from SD
2020-11-30 fixed datatype of OSM camera IDs
2020-12-04 forced to use osm ids as hex value strings, 32 bit long max
2020-12-04 reworked case
2020-12-05 small improvements to case top
2020-12-08 non "short record" ndef type
    up to 3000 bytes via NFC PogChamp
2020-12-09 fixed ndef length fields
2020-12-22 demo changes
2021-03-13 fixed KiCad library issues
2021-05-14 updated 3D files + exported schematic
2021-06-19 prep for rework
2021-06-30 added ESP D4 variant
2021-07-15 images
2021-07-15 case reworks
2021-07-16 improved image backgrounds
2021-07-28 improved image edges
2021-08-05 d4 case updates
2021-08-05 added software changes for BMA400
2021-08-11 small updates to PCB and case
2021-09-08 Create LICENCES
2021-09-16 small improvements to the case
2021-09-16 restructuring folders
2021-09-20 added tap to log location data example
    0 mA when double tapped
2021-09-20 LED and better GPS sleep in tap example
2021-10-11 file cleanup
2021-11-15 added new example + images
2021-11-15 added image to readme
2022-01-14 added expansion and JST
2022-01-14 changed voltage divider routing
2022-01-17 3v3 plane cleanup
2022-01-23 v 0.3.1 PCB
2022-01-23 added .zip to gitignore
2022-02-18 added new 3D case + PCB rework
2022-06-06 pre rework
2022-07-13 PCB redesign
2022-09-10 moving passives around BQ25181
2022-12-10 update RF430 package to VQFN
2022-12-11 reorganize passives
2023-01-15 BQ25180 redesign
2023-01-15 lower clearance for GND fills
2023-06-04 BQ25181 changes
2023-06-10 pre-production run
2023-06-20 remove hand soldering footprints
2023-10-17 certification test
2024-11-08 new footprints
2024-11-21 update text + add panel for production
2024-11-21 correct panel to 2x2
2024-11-22 update RF430 footprint
2024-11-22 update BMA400 +BQ25180 footprints
2024-11-22 update panel
2024-11-25 repair project + update 3D model path for KiCad 8
2024-11-25 add panel in seperate folder
2024-11-27 add markings
2024-11-28 update panel + panel config
2025-08-02 add new footprints
2025-08-03 update SMA footprint with matching cutout
2025-08-07 footprints + symbols
2025-09-10 new symbol + footprint
2025-11-08 Hirose FPC conn footprint
2026-05-02 add DF40 connector footprints
2026-05-04 new symbol
2026-05-06 new symbols
2026-05-09 add footprints
